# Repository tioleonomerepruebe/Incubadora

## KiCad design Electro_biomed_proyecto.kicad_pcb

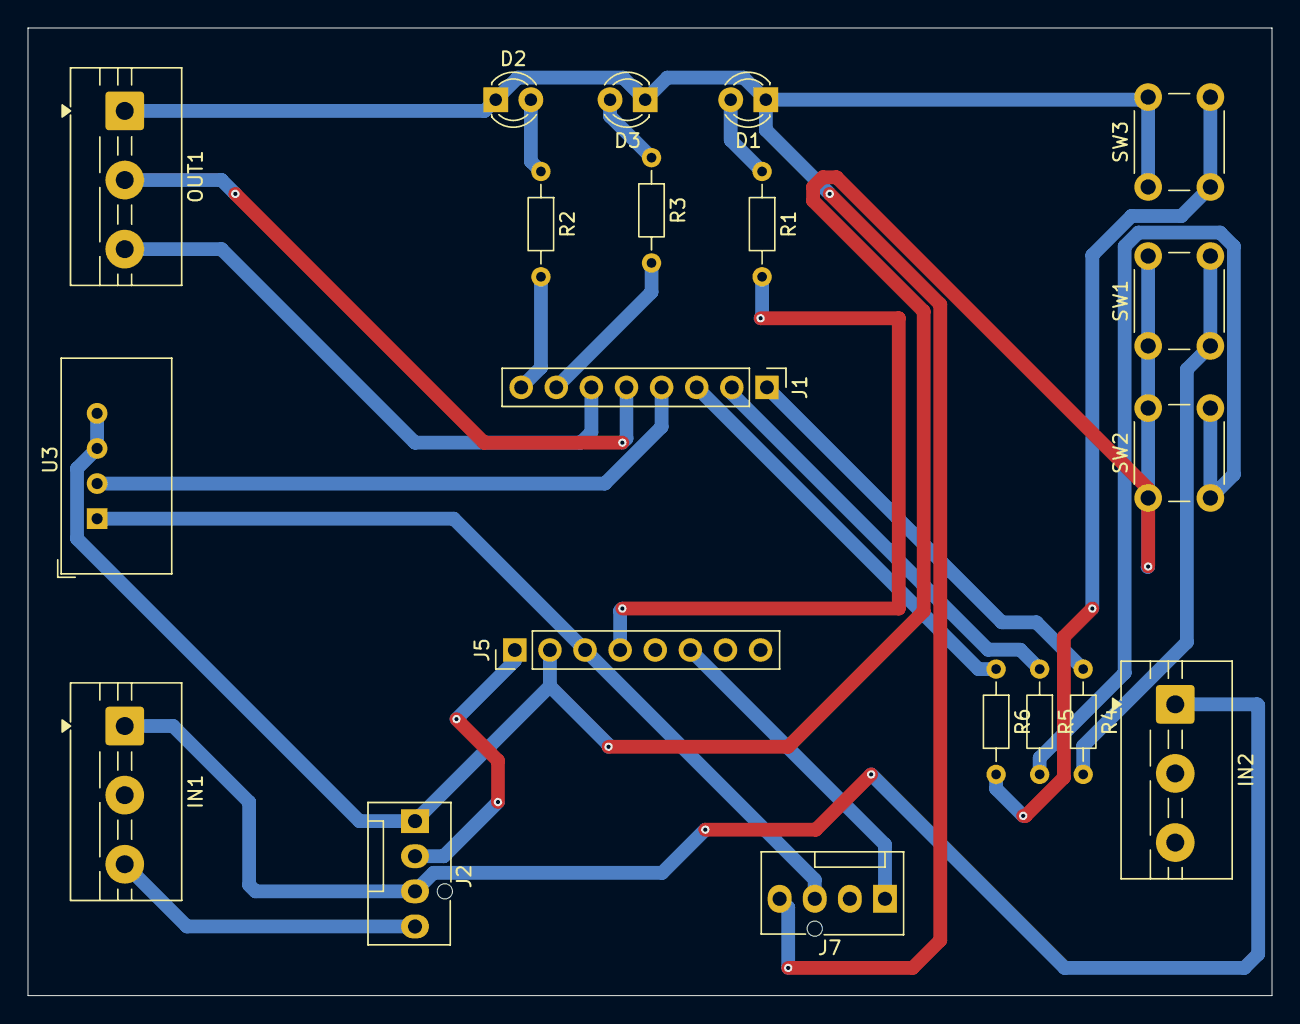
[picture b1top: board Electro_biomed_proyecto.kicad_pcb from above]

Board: 2 copper layers, 90.0 x 70.0 mm, 20 parts (0 on the bottom side), 22 nets.

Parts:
D1, D2, D3: LED; LED_D3.0mm
IN1, IN2: Screw_Terminal_01x03; TerminalBlock_MaiXu_MX126-5.0-03P_1x03_P5.00mm
J1, J5: Conn_01x08_Socket; PinHeader_1x08_P2.54mm_Vertical
J2, J7: Conn_01x04_Socket; FanPinHeader_1x04_P2.54mm_Vertical
OUT1: Screw_Terminal_01x03; TerminalBlock_MaiXu_MX126-5.0-03P_1x03_P5.00mm
R1, R2, R3, R4, R5, R6: R; R_Axial_DIN0204_L3.6mm_D1.6mm_P7.62mm_Horizontal
SW1: SET; SW_PUSH_6mm_H5mm
SW2: DOWN; SW_PUSH_6mm_H5mm
SW3: UP; SW_PUSH_6mm_H5mm
U3: AM2302; ASAIR_AM2302_P2.54mm_Vertical

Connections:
/3V3: J5.3, J7.3, U3.1 (VDD)
/5V: J2.2, J5.1
/12V: IN1.3, J2.4
/GND: J2.1, J5.2, SW1.1, SW2.1, U3.3 (GND), U3.4 (GND)
/GNDin: IN1.1, IN2.1 (Pin_1_1), J2.3
/GNDout: D1.1 (K), D2.1 (K), D3.1 (K), J7.4, OUT1.1, SW3.1
/IO0: J1.8, R2.2
/IO1: J1.7, R3.2
/IO2: J1.6, OUT1.3
/IO3: J1.5, OUT1.2
/IO4: J1.4, U3.2 (SDA)
/IO5: J1.3, R6.1
/IO6: J1.2, R5.1
/IO7: J1.1, R4.1
/IO8: J5.6, J7.1
/IO10: J5.4, R1.2
unnamed: D1.2 (A), R1.1
unnamed: D2.2 (A), R2.1
unnamed: D3.2 (A), R3.1
unnamed: R4.2, SW1.2
unnamed: R5.2, SW2.2
unnamed: R6.2, SW3.2
